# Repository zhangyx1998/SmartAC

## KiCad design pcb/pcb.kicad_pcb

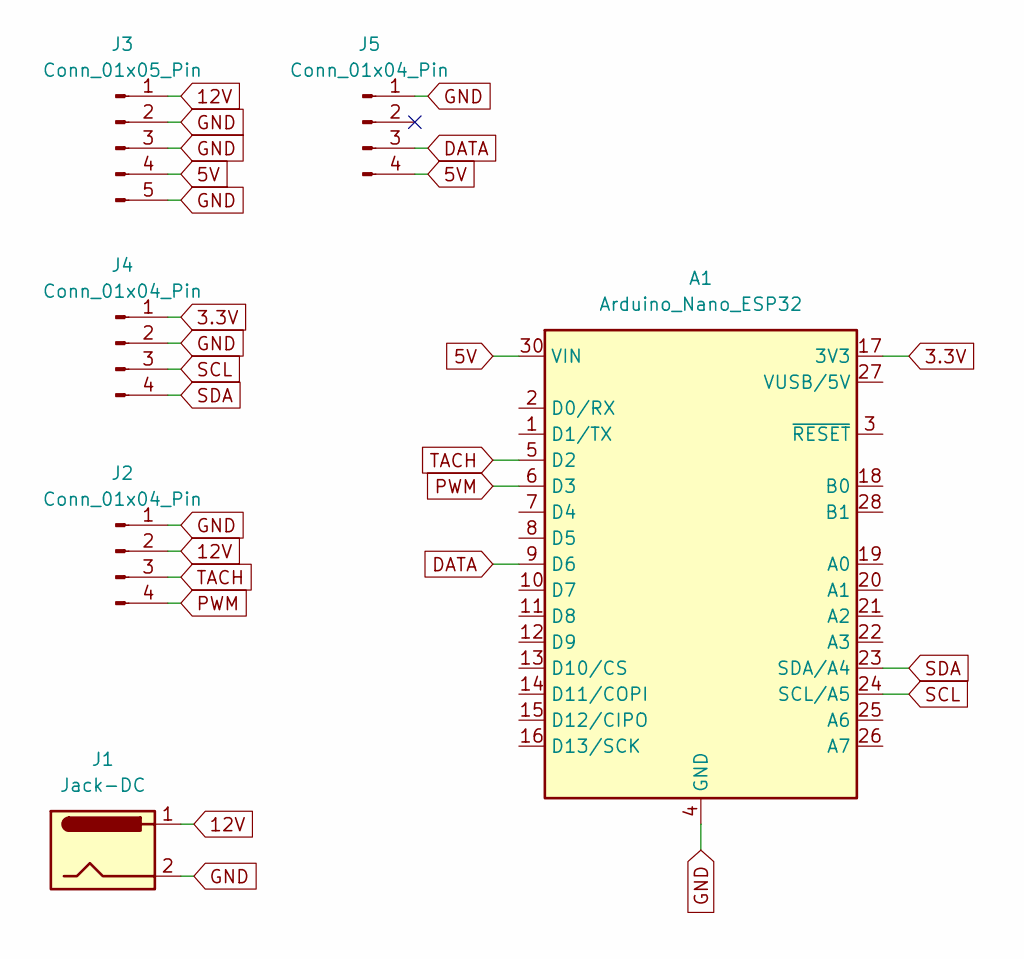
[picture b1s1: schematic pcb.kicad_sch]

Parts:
A1: Arduino_Nano_ESP32; Arduino_Nano
J1: Jack-DC; BarrelJack_Wuerth_6941xx301002
J2: Conn_01x04_Pin; Molex_KK-254_AE-6410-04A_1x04_P2.54mm_Vertical
J3: Conn_01x05_Pin; PinHeader_1x05_P2.54mm_Vertical
J4, J5: Conn_01x04_Pin; PinHeader_1x04_P2.54mm_Vertical

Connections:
3.3V: A1.17 (3V3), J4.1
5V: A1.30 (VIN), J3.4, J5.4
12V: J1.1, J2.2, J3.1
DATA: A1.9 (D6), J5.3
GND: A1.4 (GND), A1.29 (GND), J1.2, J2.1, J3.2, J3.3, J3.5, J4.2, J5.1
PWM: A1.6 (D3), J2.4
SCL: A1.24 (SCL/A5), J4.3
SDA: A1.23 (SDA/A4), J4.4
TACH: A1.5 (D2), J2.3

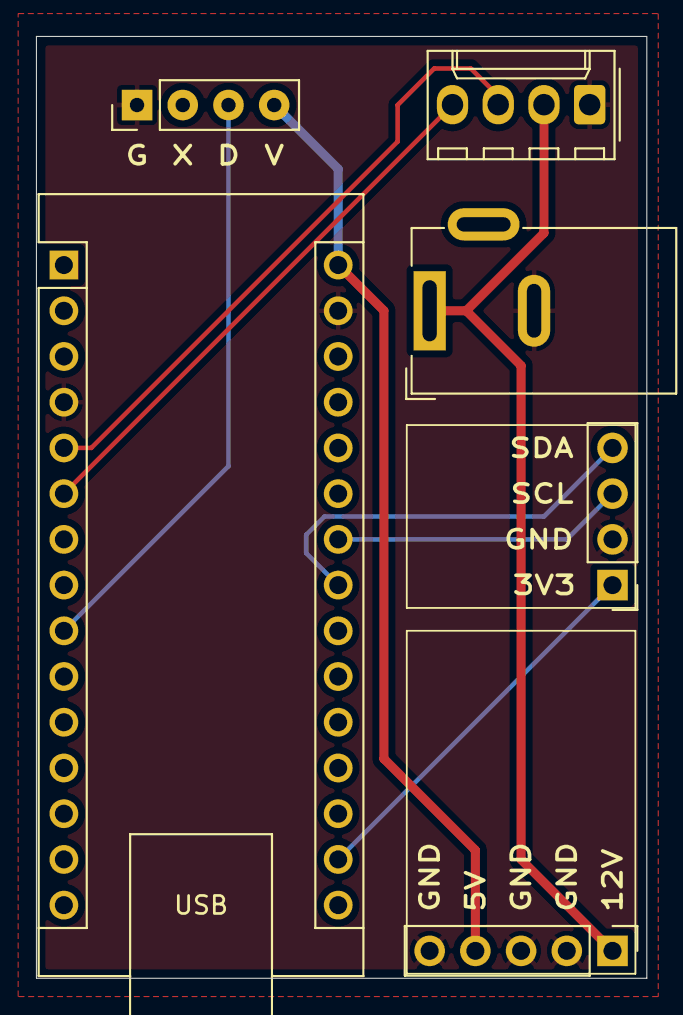
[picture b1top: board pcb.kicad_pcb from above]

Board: 2 copper layers, 33.9 x 52.3 mm, 6 parts (0 on the bottom side), 9 nets.

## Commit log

2025-12-08 update: all systems working
2025-12-08 update: frontend appearance
2025-12-08 feat: history chart
2025-12-08 feat/firmware: add utility `dig` and `ping` to serial console
2025-12-08 update/sever: cosmetic improvements
2025-12-09 update/frontend: minor improvements on history chart
